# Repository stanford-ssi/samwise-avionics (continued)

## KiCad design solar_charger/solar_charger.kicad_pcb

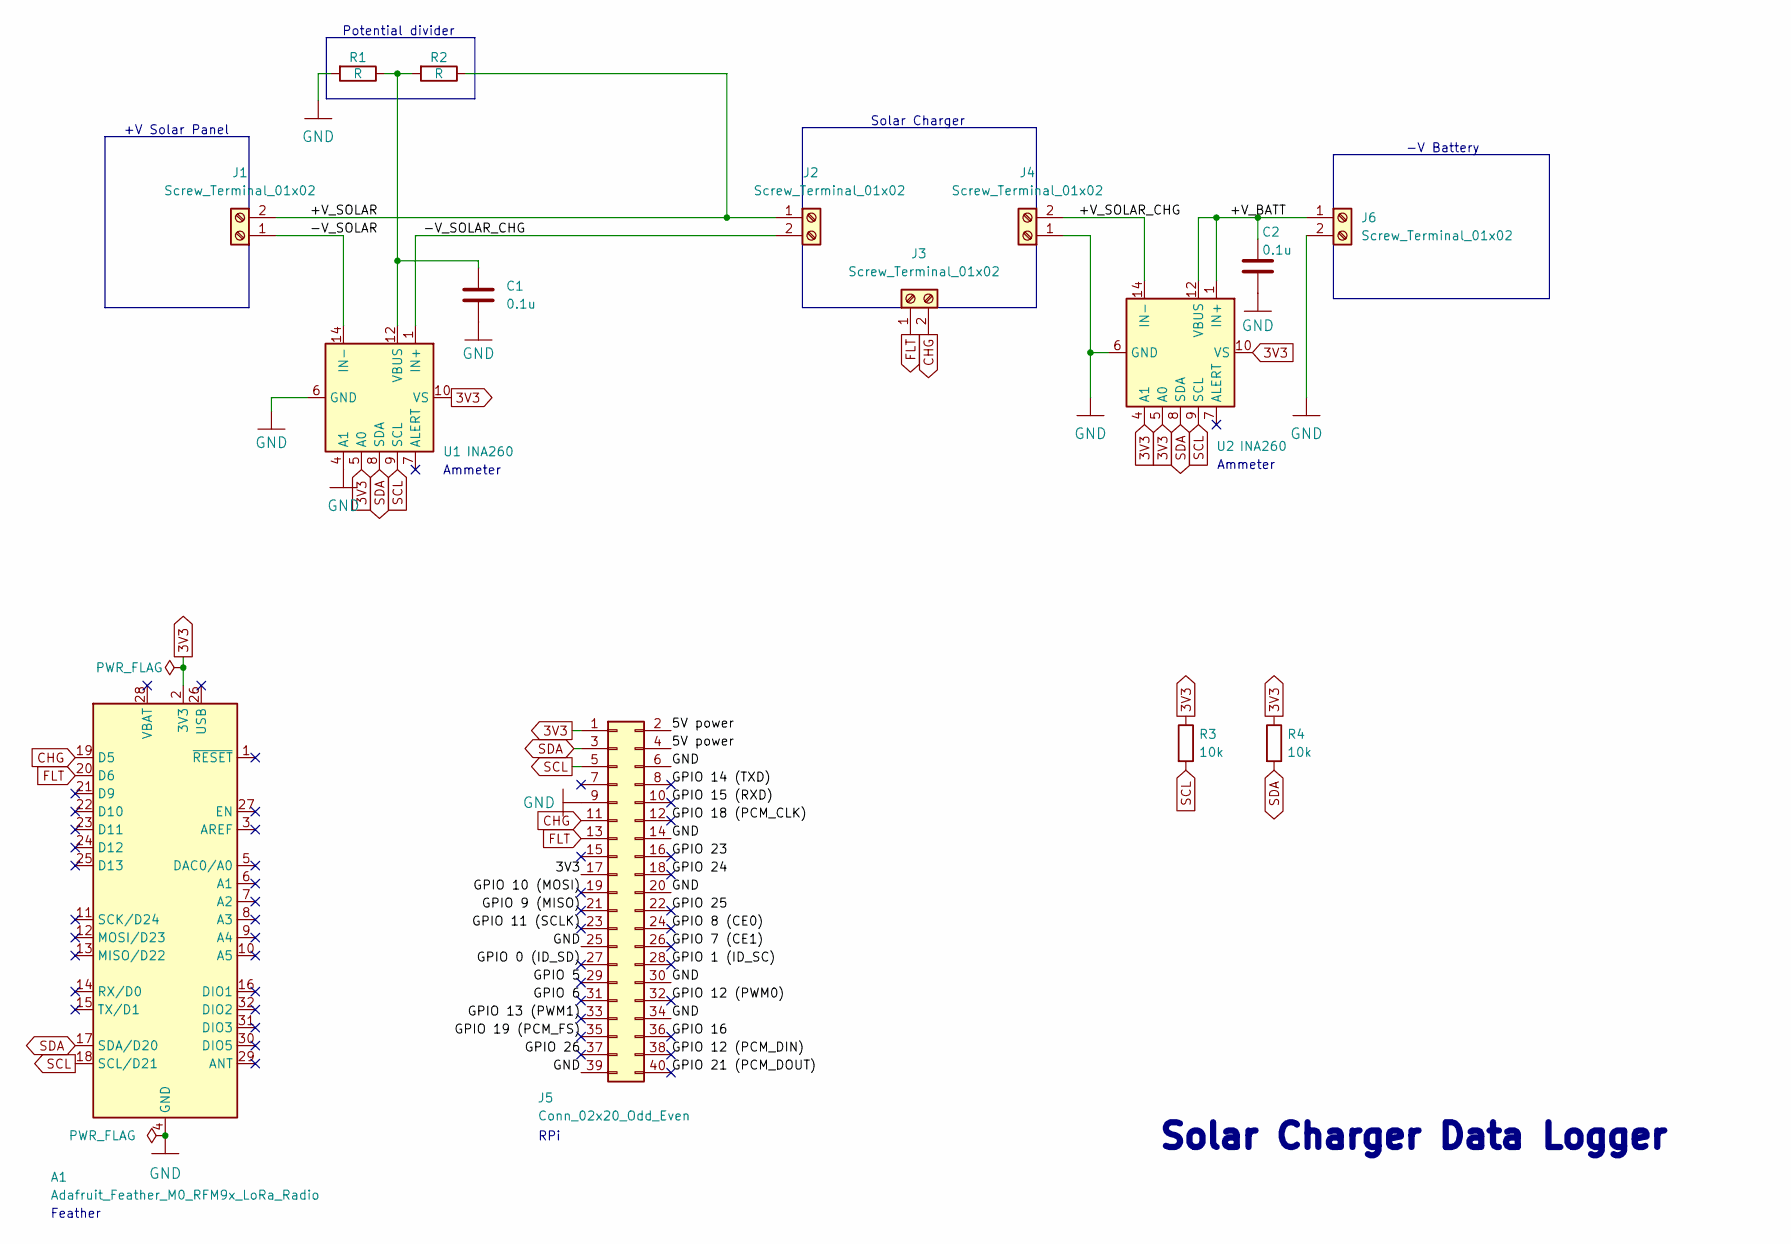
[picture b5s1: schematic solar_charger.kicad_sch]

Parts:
A1: Adafruit_Feather_M0_RFM9x_LoRa_Radio; Adafruit_Feather_M0_RFM
C1, C2: 0.1u; C_0603_1608Metric
J1, J2, J3, J4, J6: Screw_Terminal_01x02; SCREWTERMINAL-3.5MM-2_LOCK
J5: Conn_02x20_Odd_Even; PinSocket_2x20_P2.54mm_Vertical
R1, R2: R; R_0603_1608Metric
R3, R4: 10k; R_0603_1608Metric
U1, U2: INA260; TSSOP-16_4.4x5mm_P0.65mm

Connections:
3V3: A1.2 (3V3), J5.1, J5.17, R3.1, R4.1, U1.5 (A0), U1.10 (VS), U2.4 (A1), U2.5 (A0), U2.10 (VS)
/5V power: J5.2, J5.4
/+V_BATT: C2.1, J6.1, U2.1 (IN+), U2.2 (IN+), U2.3 (IN+), U2.12 (VBUS)
/+V_SOLAR: J1.2, J2.1, R2.1
/+V_SOLAR_CHG: J4.2, U2.14 (IN-), U2.15 (IN-), U2.16 (IN-)
/-V_SOLAR: J1.1, U1.14 (IN-), U1.15 (IN-), U1.16 (IN-)
/-V_SOLAR_CHG: J2.2, U1.1 (IN+), U1.2 (IN+), U1.3 (IN+)
/GPIO 0 (ID_SD): J5.27
/GPIO 1 (ID_SC): J5.28
/GPIO 5: J5.29
/GPIO 6: J5.31
/GPIO 7 (CE1): J5.26
/GPIO 8 (CE0): J5.24
/GPIO 9 (MISO): J5.21
/GPIO 10 (MOSI): J5.19
/GPIO 11 (SCLK): J5.23
/GPIO 12 (PCM_DIN): J5.38
/GPIO 12 (PWM0): J5.32
/GPIO 13 (PWM1): J5.33
/GPIO 14 (TXD): J5.8
/GPIO 15 (RXD): J5.10
/GPIO 16: J5.36
/GPIO 18 (PCM_CLK): J5.12
/GPIO 19 (PCM_FS): J5.35
/GPIO 21 (PCM_DOUT): J5.40
/GPIO 23: J5.16
/GPIO 24: J5.18
/GPIO 25: J5.22
/GPIO 26: J5.37
CHG: A1.19 (D5), J3.2, J5.11
FLT: A1.20 (D6), J3.1, J5.13
GND: A1.4 (GND), C1.2, C2.2, J4.1, J5.6, J5.9, J5.14, J5.20, J5.25, J5.30, J5.34, J5.39, J6.2, R1.2, U1.4 (A1), U1.6 (GND), U1.11 (GND), U2.6 (GND), U2.11 (GND)
unnamed: C1.1, R1.1, R2.2, U1.12 (VBUS)
SCL: A1.18 (SCL/D21), J5.5, R3.2, U1.9 (SCL), U2.9 (SCL)
SDA: A1.17 (SDA/D20), J5.3, R4.2, U1.8 (SDA), U2.8 (SDA)

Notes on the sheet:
Ammeter
Potential divider
-V Battery
Feather
RPi
Ammeter
Solar Charger Data Logger
Solar Charger
+V Solar Panel

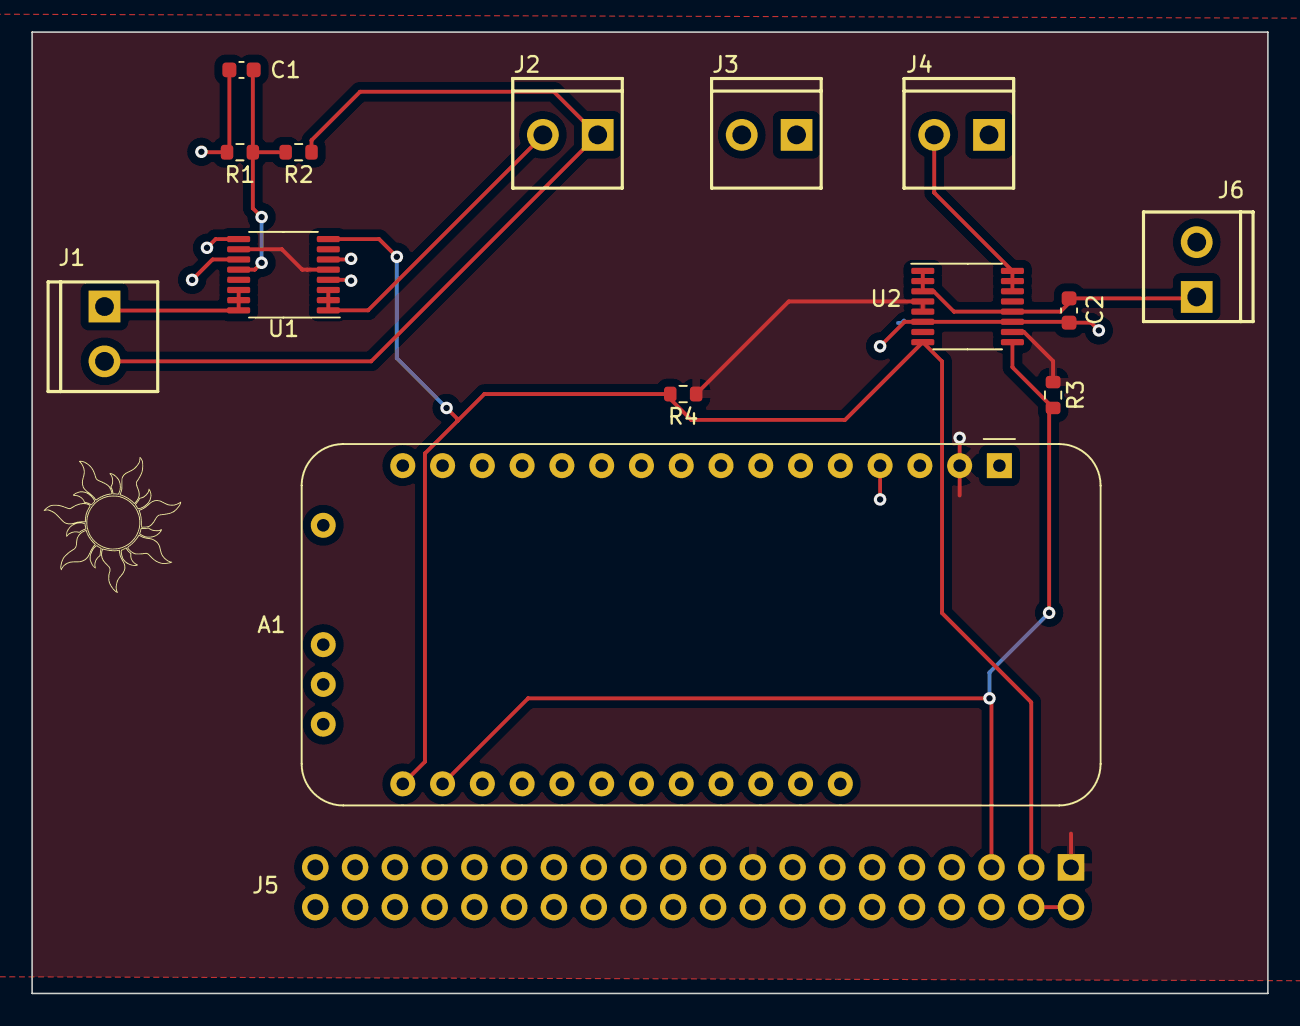
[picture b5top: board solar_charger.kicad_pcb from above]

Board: 4 copper layers, 78.9 x 61.4 mm, 15 parts (1 on the bottom side), 13 nets.

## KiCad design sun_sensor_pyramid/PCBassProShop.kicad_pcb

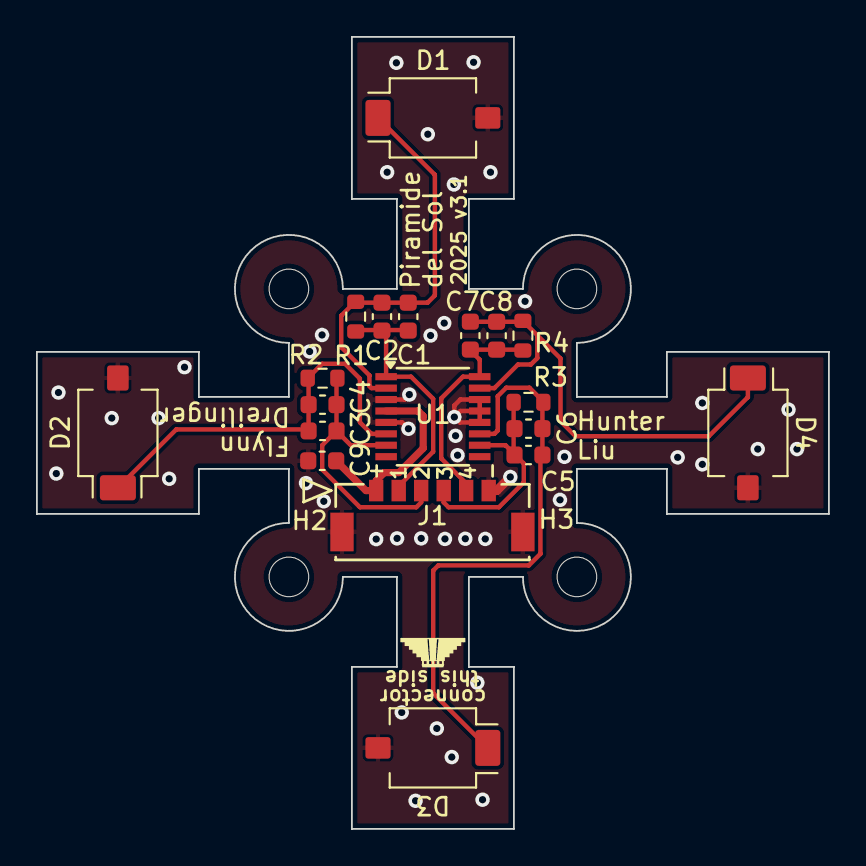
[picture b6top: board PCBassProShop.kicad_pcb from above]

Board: 2 copper layers, 44.0 x 44.0 mm, 23 parts (0 on the bottom side), 10 nets.

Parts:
C1, C3, C5, C7: 1nF; C_0603_1608Metric
C2, C4, C6, C8, C9: 100nF; C_0603_1608Metric
D1, D2, D3, D4: SFH2430; Osram_SFH2430
H1, H2, H3, H4: MountingHole_Pad; MountingHole_2.2mm_M2
J1: 505567-0631; Molex_505567-0631
R1, R2, R3, R4: 3.9k; R_0603_1608Metric
U1: LTC2052HGN_PBF; SSOP-16_3.9x4.9mm_P0.635mm

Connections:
+3V3: C9.1, J1.1, U1.4 (V+)
/OUT1: C1.2, C2.2, J1.2, R1.2, U1.1 (OUTA)
/OUT2: C3.2, C4.2, J1.3, R2.2, U1.7 (OUTB)
/OUT3: C5.2, C6.2, J1.4, R3.2, U1.10 (OUTC)
/OUT4: C7.2, C8.2, J1.5, R4.2, U1.16 (OUTD)
/Photodiode 1/IN-: C1.1, C2.1, D1.1 (K), R1.1, U1.2 (-INA)
/Photodiode 2/IN-: C3.1, C4.1, D2.1 (K), R2.1, U1.6 (-INB)
/Photodiode 3/IN-: C5.1, C6.1, D3.1 (K), R3.1, U1.11 (-INC)
/Photodiode 4/IN-: C7.1, C8.1, D4.1 (K), R4.1, U1.15 (-IND)
GND: C9.2, D1.2 (A), D2.2 (A), D3.2 (A), D4.2 (A), J1.6, J1.7 (Shield), J1.8 (Shield), U1.3 (+INA), U1.5 (+INB), U1.12 (+INC), U1.13 (V-), U1.14 (+IND)

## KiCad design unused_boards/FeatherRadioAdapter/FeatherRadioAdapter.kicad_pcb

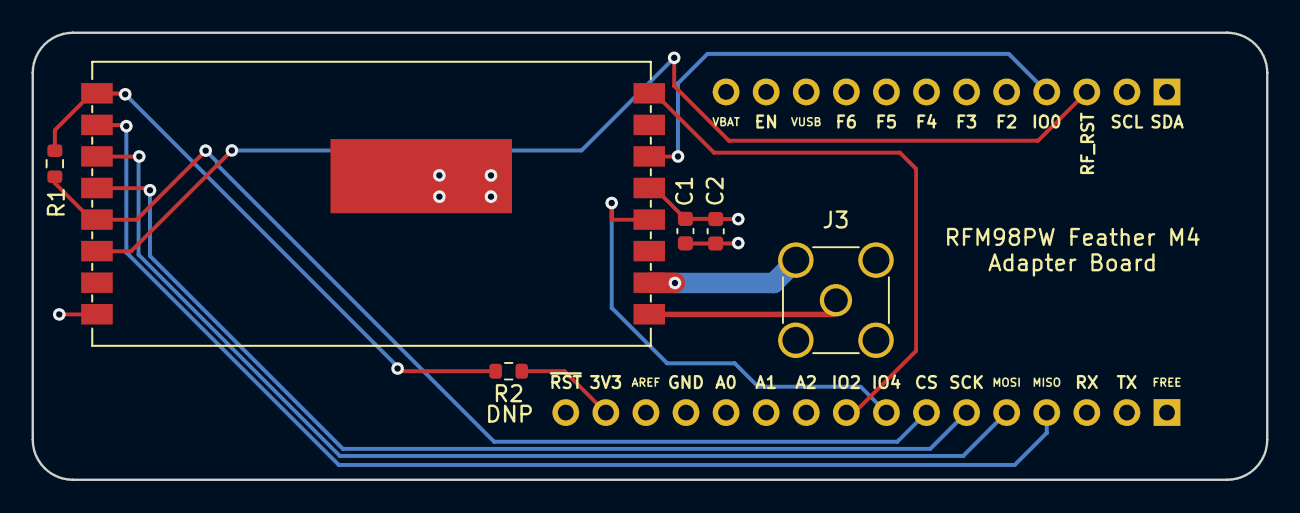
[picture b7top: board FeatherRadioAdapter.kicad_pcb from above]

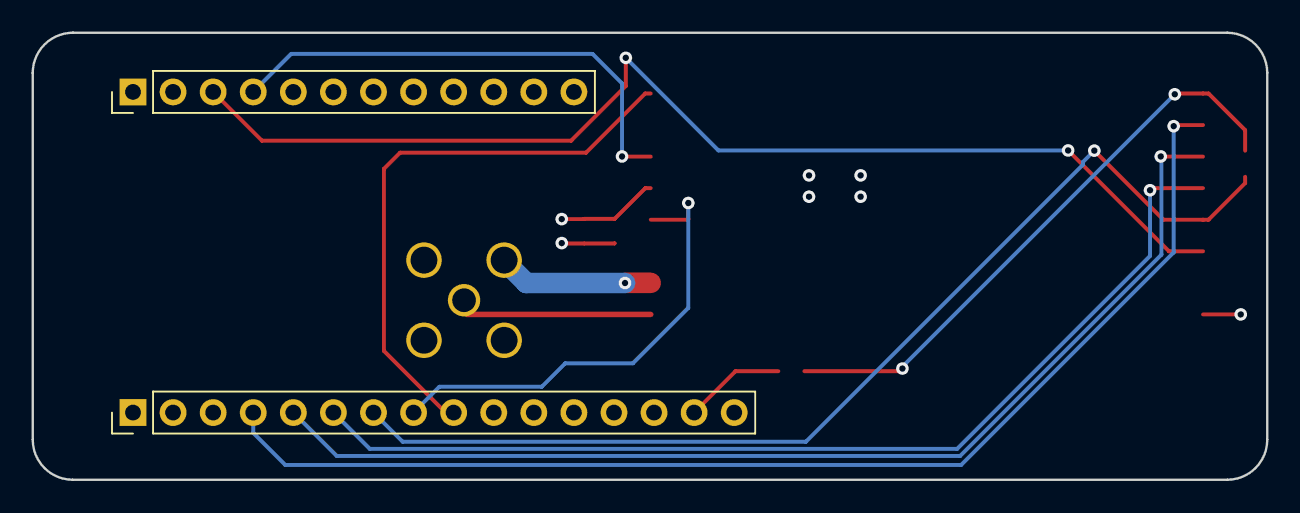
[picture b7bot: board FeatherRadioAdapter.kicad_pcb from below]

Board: 4 copper layers, 78.2 x 28.3 mm, 8 parts (2 on the bottom side), 13 nets.

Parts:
C1: 0.1uF; C_0603_1608Metric
C2: 10uF; C_0603_1608Metric
J1: feather long; PinHeader_1x16_P2.54mm_Vertical
J2: feather short; PinHeader_1x12_P2.54mm_Vertical
J3: Amphenol_901-144; SMA_Amphenol_901-144_horizontal
R1: 10k; R_0603_1608Metric
R2: 0; R_0603_1608Metric
U1: RFM98PW

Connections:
3.3V: R1.1, R2.2, U1.9 (3.3V)
+3V3: J1.15, R2.1
/CS: J1.7, R1.2, U1.13 (NSS)
/MISO: J1.4, U1.10 (MISO)
/MOSI: J1.5, U1.11 (MOSI)
/RF1_ANT: J3.1 (In), U1.1 (ANT)
/RF_IO0: J2.4, U1.6 (GPIO_0)
/RF_IO2: J1.9, U1.8 (GPIO_2)
/RF_IO4: J1.8, U1.4 (GPIO_4)
/RF_RST: J2.3, U1.14 (RESET)
/SCK: J1.6, U1.12 (SCK)
/VUSB: C1.2, C2.2, J2.10, U1.5 (VCC)
GND: C1.1, C2.1, J1.13, J3.2 (Ext), U1.2 (GND), U1.16 (GND), U1.17 (GND)
